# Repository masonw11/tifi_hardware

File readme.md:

## Attributions
This project contains design files obtained from [SnapEDA](https://www.snapeda.com/home/). These models are used as-is. SnapEDA permits publicly redistributing up to 10 models.

SnapEDA licenses these models under a Creative Commons Attribution-ShareAlike 4.0 International License (CC BY-SA) with Design Exception 1.0. This license can be found in the project wherever their models are included.

The following models in the project were obtained from SnapEDA:
- [SM04B-SRSS-TB(LF)(SN)](https://www.snapeda.com/parts/SM04B-SRSS-TB(LF)(SN)/JST%20SALES%20AMERICA%20INC%20(VA)/view-part/?ref=digikey) (also referred to as STEMMA QT within the project)
- [SHT40-AD1B-R2](https://www.snapeda.com/parts/SHT40-AD1B-R2/Sensirion/view-part/?ref=digikey)

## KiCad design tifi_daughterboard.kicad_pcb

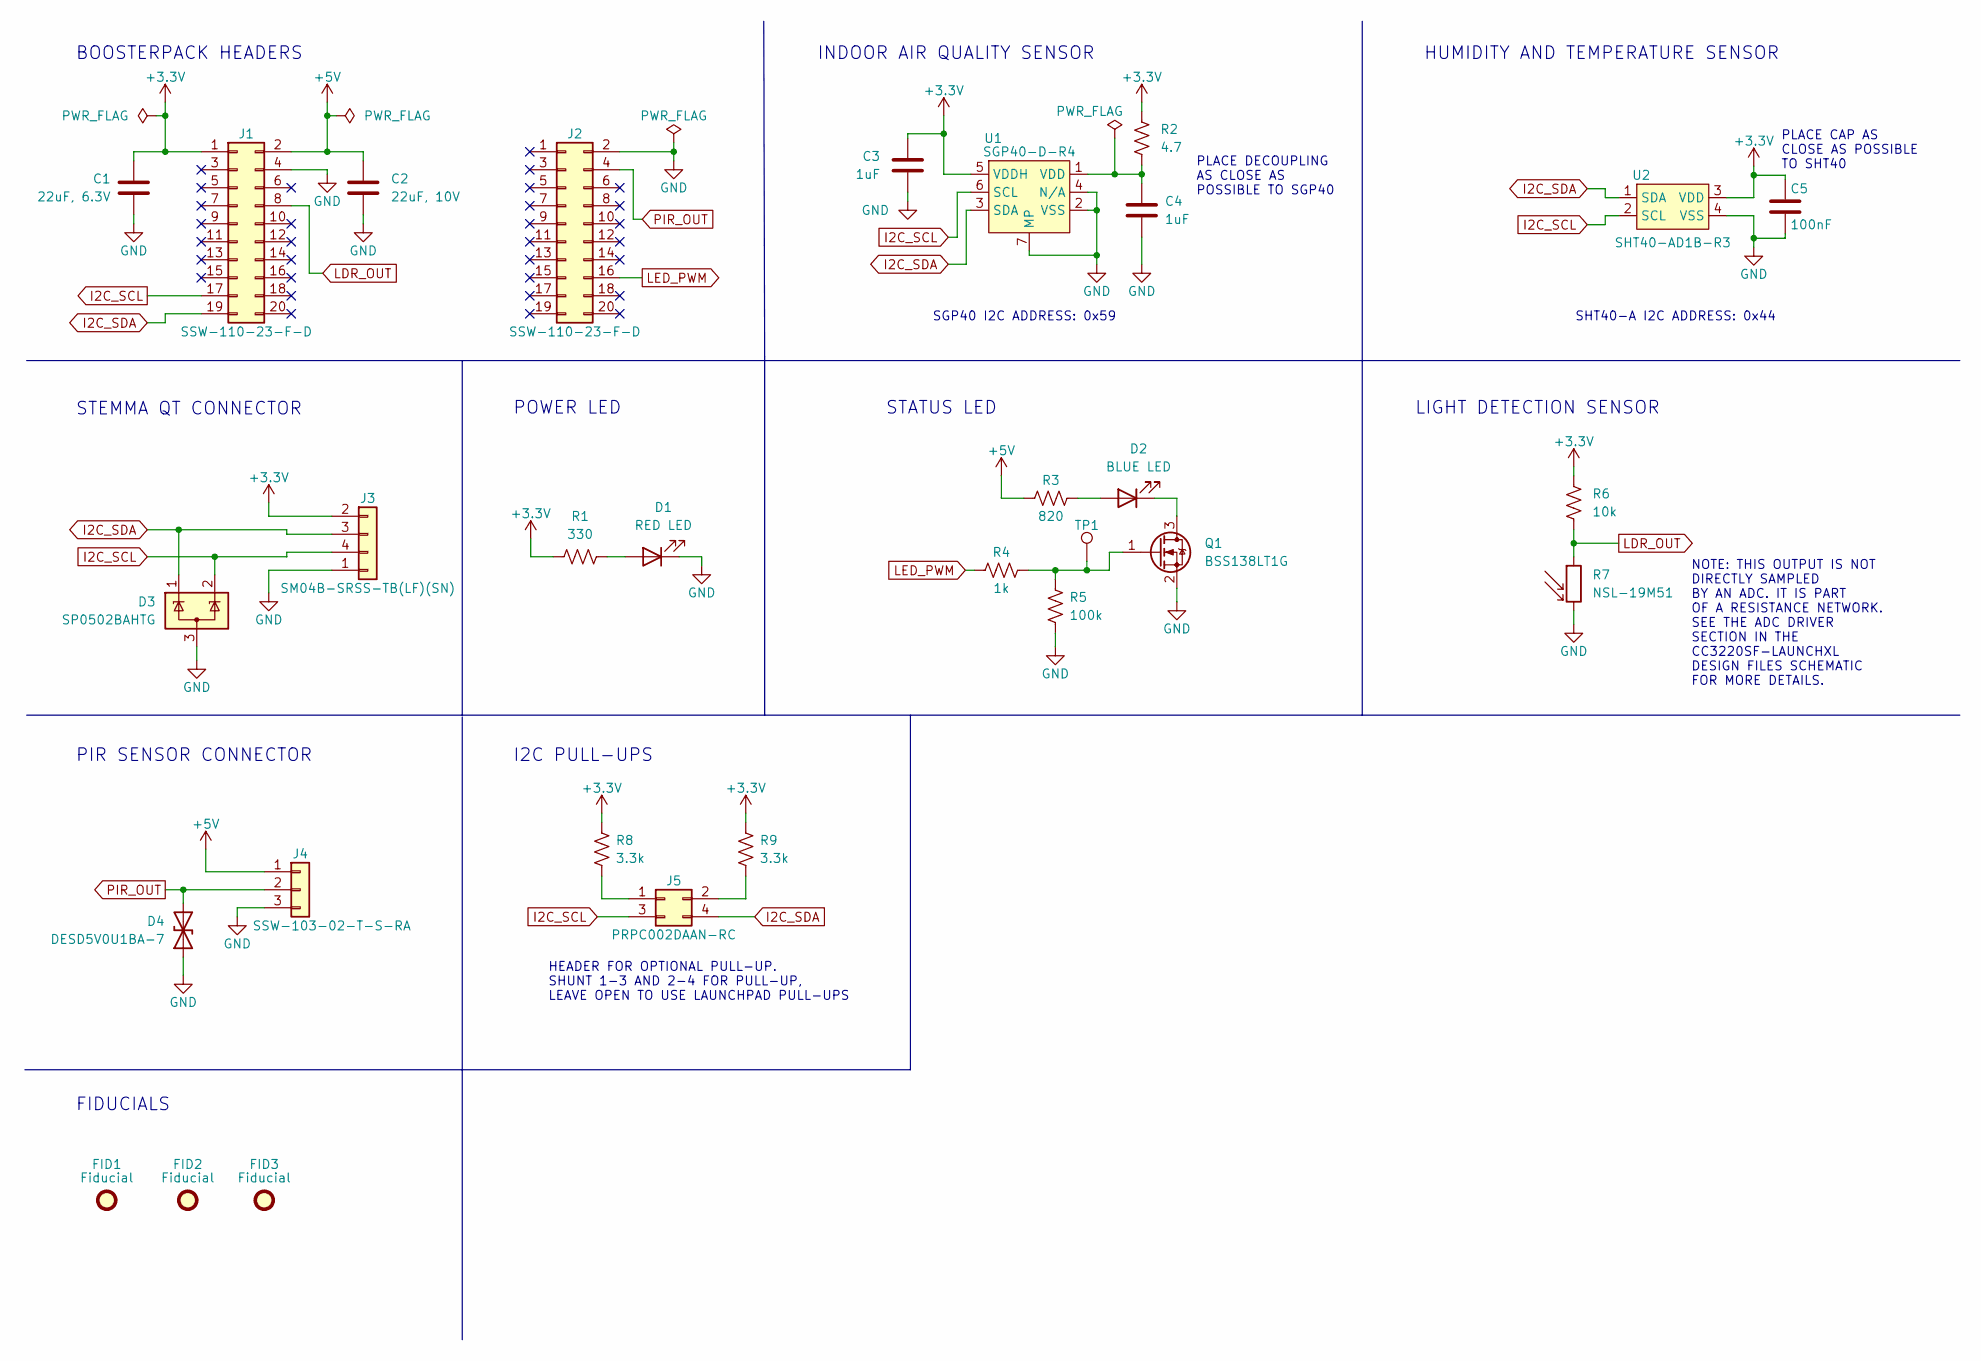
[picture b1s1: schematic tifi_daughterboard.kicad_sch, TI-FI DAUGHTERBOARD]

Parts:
C1: 22uF, 6.3V; C_1206_3216Metric
C2: 22uF, 10V; C_1206_3216Metric
C3, C4: 1uF; C_0805_2012Metric
C5: 100nF; C_0805_2012Metric
D1: RED LED; LED_0805_2012Metric_Pad1.15x1.40mm_HandSolder
D2: BLUE LED; LED_0805_2012Metric_Pad1.15x1.40mm_HandSolder
D3: SP0502BAHTG; SOT-23
D4: DESD5V0U1BA-7; D_SOD-323
FID1, FID2, FID3: Fiducial; Fiducial_1mm_Mask2mm
J1, J2: SSW-110-23-F-D; PinHeader_2x10_P2.54mm_Vertical
J3: SM04B-SRSS-TB(LF)(SN); JST_SM04B-SRSS-TB(LF)(SN)
J4: SSW-103-02-T-S-RA; PinSocket_1x03_P2.54mm_Horizontal
J5: PRPC002DAAN-RC; PinHeader_2x02_P2.54mm_Vertical
Q1: BSS138LT1G; SOT-23
R1: 330; R_0805_2012Metric
R2: 4.7; R_0805_2012Metric
R3: 820; R_0805_2012Metric
R4: 1k; R_0805_2012Metric
R5: 100k; R_0805_2012Metric
R6: 10k; R_0805_2012Metric
R7: NSL-19M51; R_LDR_4.9x4.2mm_P2.54mm_Vertical
R8, R9: 3.3k; R_0805_2012Metric
TP1: TestPoint; TestPoint_THTPad_D1.5mm_Drill1.0mm
U1: SGP40-D-R4; DFN-6-1EP_2.44x2.44mm_P0.8mm_EP1.25x1.7mm
U2: SHT40-AD1B-R3; XDCR_SHT40-AD1B-R2

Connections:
+3.3V: C1.1, C3.1, C5.1, J1.1, J3.2, R1.1, R2.1, R6.1, R8.1, R9.1, U1.5 (VDDH), U2.3 (VDD)
+5V: C2.1, J1.2, J4.1, R3.1
GND: C1.2, C2.2, C3.2, C4.2, C5.2, D1.1 (K), D3.3 (A), D4.1 (A1), J1.4, J2.2, J3.1, J4.3, Q1.2 (S), R5.2, R7.2, U1.2 (VSS), U1.4 (N/A), U1.7 (MP), U2.4 (VSS)
I2C_SCL: D3.2 (K), J1.17, J3.4, J5.3, U1.6 (SCL), U2.2 (SCL)
I2C_SDA: D3.1 (K), J1.19, J3.3, J5.4, U1.3 (SDA), U2.1 (SDA)
LDR_OUT: J1.8, R6.2, R7.1
LED_PWM: J2.16, R4.1
unnamed: C4.1, R2.2, U1.1 (VDD)
unnamed: D1.2 (A), R1.2
unnamed: D2.1 (K), Q1.3 (D)
unnamed: D2.2 (A), R3.2
unnamed: J5.1, R8.2
unnamed: J5.2, R9.2
unnamed: Q1.1 (G), R4.2, R5.1, TP1.1
PIR_OUT: D4.2 (A2), J2.4, J4.2

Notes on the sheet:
POWER LED
PLACE DECOUPLING AS CLOSE AS POSSIBLE TO SGP40
SHT40-A I2C ADDRESS: 0x44
SGP40 I2C ADDRESS: 0x59
STATUS LED
PLACE CAP AS CLOSE AS POSSIBLE TO SHT40
LIGHT DETECTION SENSOR
PIR SENSOR CONNECTOR
STEMMA QT CONNECTOR
HUMIDITY AND TEMPERATURE SENSOR
INDOOR AIR QUALITY SENSOR
BOOSTERPACK HEADERS
HEADER FOR OPTIONAL PULL-UP. SHUNT 1-3 AND 2-4 FOR PULL-UP, LEAVE OPEN TO USE LAUNCHPAD PULL-UPS
NOTE: THIS OUTPUT IS NOT DIRECTLY SAMPLED BY AN ADC. IT IS PART OF A RESISTANCE NETWORK. SEE THE ADC DRIVER SECTION IN THE CC3220SF-LAUNCHXL DESIGN FILES SCHEMATIC FOR MORE DETAILS.
FIDUCIALS
I2C PULL-UPS

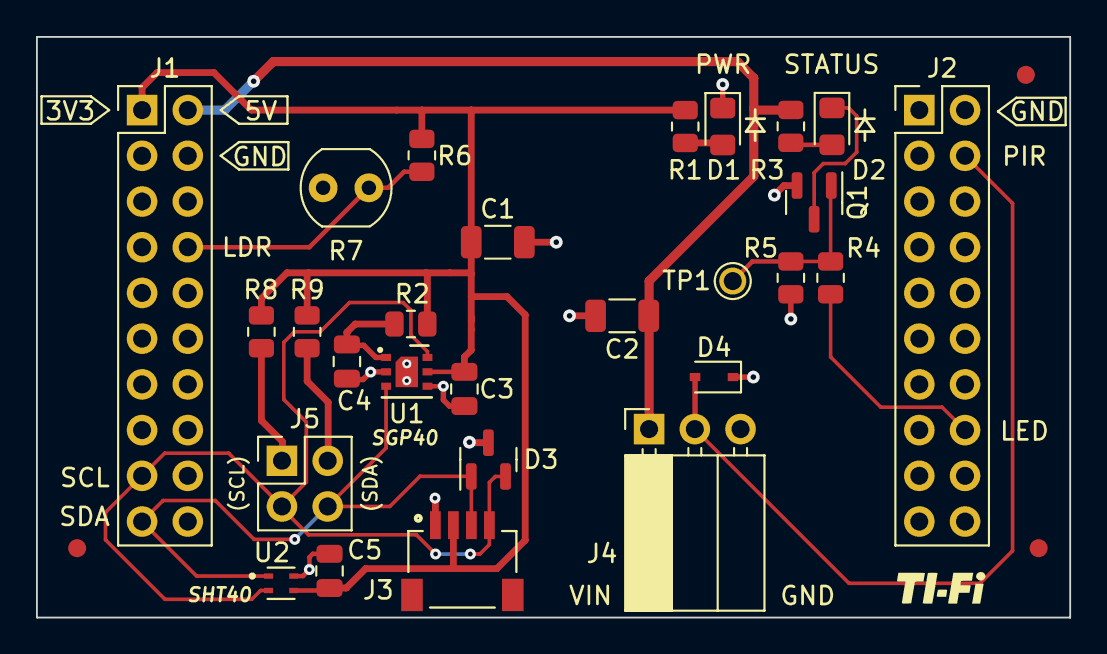
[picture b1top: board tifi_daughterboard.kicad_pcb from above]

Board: 2 copper layers, 57.4 x 32.3 mm, 30 parts (0 on the bottom side), 15 nets.

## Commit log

2022-09-01 Initial commit of project files.
2022-09-01 Add local settings to gitignore.
2022-09-01 Add BoosterPack headers to schematic.
2022-09-01 Remove backups folder and add to gitignore.
2022-09-01 Add symbol libary. Create SGP40 symbol.
2022-09-01 Add SGP40 to schematic.
2022-09-02 Add datasheet to SGP40 symbol.
2022-09-02 Create SHT40 symbol.
2022-09-02 Rearrange SHT40 pins.
2022-09-02 Add SHT40 and todos to schematic.
2022-09-15 added ldr symbol
2022-09-15 Added PIR and Testpoint, haven't annotated or footprinted yet
2022-09-15 Changed the input/output of the ldr
2022-09-20 Updating PIR circuit
2022-09-20 Added the values for the regulator components
2022-09-20 added footprints
2022-09-22 Added JST connector for stemma
2022-09-26 Add autosaved files to gitignore
2022-09-27 Change STEMMA QT connector.
    The previous connector had 2mm pitch, changed to 1mm pitch.
2022-09-27 Corrected pitch on BoosterPack headers footprint.
    The previous pitch is 1mm, needed to be 2.54mm.
2022-09-27 Update PIR sensor connector.
2022-09-28 Increase section labels to 70 mils.
2022-09-28 Various polish fixes and ADC pin correction.
    Removed unused net label.
    Added NC flags to headers.
    Moved LDR circuit output to ADC pin supported on the CC3220SF LaunchPad.
    Update LDR symbol and footprint to use KiCad built-ins.
2022-09-28 Add STEMMA QT footprint and attributions.
2022-09-29 Light level sensor fix.
    Output was previously obtained from a net connected to GND.
    The design now uses a voltage divider.
2022-09-29 Generic cleanup.
    Removed test points temporarily until schematic is feature-complete.
    Added PWR_FLAG to BoosterPack power pins for ERC check.
2022-09-29 Assign parts to BP headers. Add power LED.
2022-09-30 Add indicator LED circuit.
2022-09-30 Add series gate resistor to LED PWM circuit.
2022-09-30 Annotate schematic references
2022-09-30 Assign footprints to discrete components.
2022-09-30 Create SGP40 footprint
2022-09-30 Add SHT40 SnapEDA model. Assign footprint.
2022-09-30 Rough layout draft.
2022-09-30 Routing start
2022-09-30 Complete routing, still some TODOs.
    TODOS include:
    Test pads / points
    Reduce vias on I2C signals?
    TVS diodes on connectors
    Shunt option for blue LED (bypass PWM)
    Optional I2C pullups
2022-10-01 Move to 4-layer stackup.
2022-10-01 Start 4-layer routing.
2022-10-02 Revert to two layers. Move PIR sensor output.
2022-10-02 Reposition STEMMA QT to bottom of board.
2022-10-02 Move VOC sensor closer to header.
2022-10-02 Route I2C connections.
2022-10-02 Route 5V rail
2022-10-02 Route remaining components.
2022-10-02 Adjust LED placement.
2022-10-02 Add alignment silkscreen.
2022-10-02 Add testpoint for LED driver FET gate.
2022-10-02 Zone fill update for test point.
2022-10-02 Add TVS diodes to connectors.
2022-10-02 Add useful info to silkscreen layer
2022-10-02 Add optional I2C pullups.
2022-10-03 Add logo
2022-10-03 Add mask clearance and supplier link fields.
2022-10-03 Add bulk capacitors to schmatic and board.
2022-10-03 Add board fiducials and pad to SGP40 symbol.
2022-10-04 Schematic cleanup, minor board fixes.
2022-10-06 Add purchase links for each component.
2022-10-06 Licensing
2022-10-06 Sync PCB with schematic changes.
2022-10-06 Export gerbers for Rev0
2022-10-06 Add voltage rating to bulk caps
    These caps were being collated in the BOM.
    They have seperate max voltage ratings.
2022-10-06 Update PCB with new capacitor values.
2022-11-02 Fix GND label on back silkscreen.
2022-11-02 Add diode symbol for LEDs. Reposition I2C labels.
2022-11-02 Increase net label spacing for J4.
2022-11-02 Change Q1 symbol to standard GSD pin numbering.
2022-11-02 Change minimum trace width to 8 mils.
2022-11-03 Update schematic to reflect correct Q1 numbering.
2022-11-03 Add OSHW logo to back silkscreen.
2022-11-03 Bump to revision 1.
2022-11-03 Move J5 away from J1, increase label size.
2022-11-03 Refill ground plane
2022-11-03 Fix overlapping courtyards.
2022-11-03 Refill ground plane.
2022-11-03 Generate Rev1 gerbers.
2022-11-03 Add correct 3D model for BoosterPack headers.
2022-11-03 Add Q1 datasheet.

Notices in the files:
tifi_daughterboard.kicad_pcb:
LICENSE: MIT LICENSE
